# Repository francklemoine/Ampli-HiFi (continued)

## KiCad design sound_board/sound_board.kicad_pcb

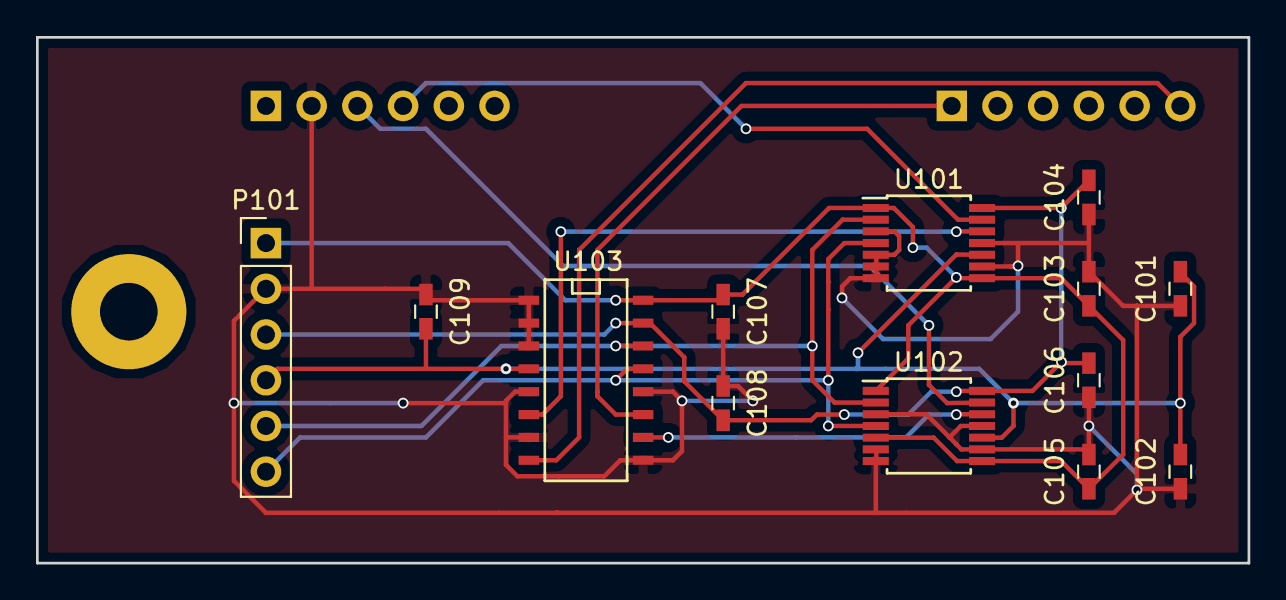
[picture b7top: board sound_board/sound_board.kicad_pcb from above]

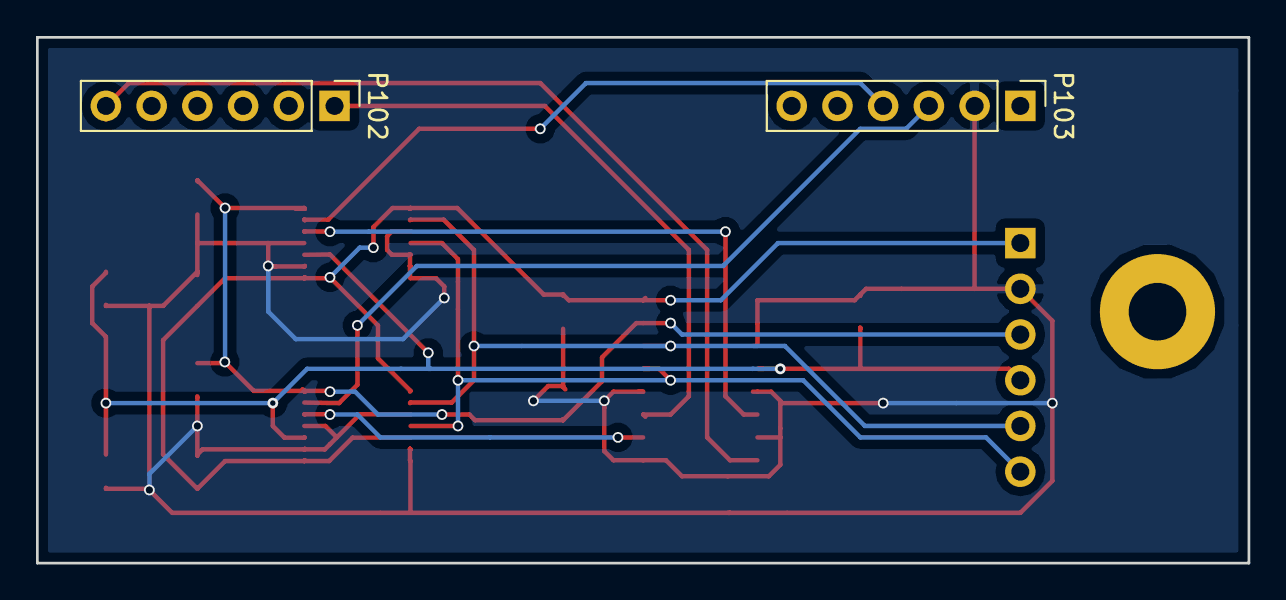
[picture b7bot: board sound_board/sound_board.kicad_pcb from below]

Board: 2 copper layers, 67.3 x 29.2 mm, 15 parts (2 on the bottom side), 12 nets.

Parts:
C101, C102, C103, C104, C105, C106, C107, C108, C109: 100nF; C_0603_HandSoldering
P101, P102, P103: CONN_01X06; Pin_Header_Straight_1x06_Pitch2.54mm
U101, U102: MCP45HVx1; TSSOP-14_4.4x5mm_Pitch0.65mm
U103: DS1808; SO-16-N

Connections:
+5V: C103.2, C105.2, C107.2, P101.1, U101.1, U101.8, U102.1, U102.5, U102.8, U103.16
+7.2V: C104.2, C106.2, C108.2, P101.3, U101.14, U102.14, U103.15
-7.2V: C101.2, C102.2, C109.2, P101.4, U101.10, U102.10, U103.4
/BAL_HIGH_L: P103.3, U102.13
/BAL_HIGH_R: P103.4, U101.13
/I2C-SCL: P101.5, U101.2, U102.2, U103.14
/I2C-SDA: P101.6, U101.4, U102.4, U103.13
/VOL_WIPPER_L: P102.1, U103.11
/VOL_WIPPER_R: P102.6, U103.8
GND: C101.1, C102.1, C103.1, C104.1, C105.1, C106.1, C107.1, C108.1, C109.1, P101.2, P103.2, U101.3, U101.5, U101.6, U101.7, U101.9, U101.11, U102.3, U102.6, U102.7, U102.9, U102.11, U103.1, U103.2, U103.3, U103.5, U103.7, U103.9, U103.12
unnamed: U101.12, U103.6
unnamed: U102.12, U103.10

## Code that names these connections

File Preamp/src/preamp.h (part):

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} state_t;

const int  ADDR_MEM_BASE         = 0;  // Arduino Mega (ATmega2560) = 4kb from 0 to 4095 / Arduino Nano (ATmega328) = 1kb
const int  LATCH_595_PIN         = A1; // Connected to ST_CP of 74HC595  -  ATMEGA328-pin24 (PC1, PCINT9)
const int  CLOCK_595_PIN         = A2; // Connected to SH_CP of 74HC595  -  ATMEGA328-pin25 (PC2, PCINT10)
const int  DATAS_595_PIN         = A0; // Connected to DS of 74HC595     -  ATMEGA328-pin23 (PC0, PCINT8)


#ifdef USE_POTENTIOMETER_CE_PIN
	const byte POT_CE_PIN        = 5;  // Connected to CE of DS18xx Numeric Potentiometer  -  ATMEGA328-pin9 (PD5, PCINT21)
#endif


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} sources_t;

// Remote Control
const byte IRECV_PIN               = 8;  // Connected to IR Receiver out pin (Atmega Pin12 = PB0)
const byte IRECV_BITS_NUMBER       = 20;
const byte IRECV_TOGGLE_NUM_BIT    = 16;
const byte IRECV_PWR               = 0x0C;
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	[C_MENU_EXIT]  = IRECV_MENU_EXIT
};

const byte AMPLIFIER_K_PIN         = A3;  // ATMEGA328-pin26 (PC3, PCINT11)
const byte PREAMPLIFIER_K_PIN      = 2;   // ATMEGA328-pin32 (PD2, PCINT18)

// LED NeoPixel
const byte NEOPIXEL_PIN            = 10;  // ATMEGA328-pin14 (PB2, PCINT2)
const byte NEOPIXEL_GND_PIN        = 3;   // ATMEGA328-pin1  (PD3, PCINT19)
const byte NEOPIXEL_NUM            = 1;   // only one led
const byte NEOPIXEL_BRIGHTNESS     = 10;
const byte NEOPIXEL_BRIGHTNESS_MAX = 250;
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
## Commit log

2017-02-04 Reorg project tree
2017-02-04 Boitier
2017-02-04 Add readme
2017-02-07 Gerber
2017-02-07 Correctifs divers
2017-02-24 Add connection board (preampli. to ampli.)
2017-03-10 Divers
2017-07-27 Arduino/Atmega Software - Initial commit
2017-07-31 Only one i2c potentiometer to manage sound
2017-09-07 DS1882 potentiometer + Divers
2017-10-20 PCB select_board
2017-10-20 PCB mcu_board: RC5 + REC-80 (panasonic) IR protocols
2017-10-20 Add IR REC-80 protocol (Atoll CD-80se2 player) + Divers
2017-10-20 Add Gerber files
2017-11-29 Avoid compilation issue
